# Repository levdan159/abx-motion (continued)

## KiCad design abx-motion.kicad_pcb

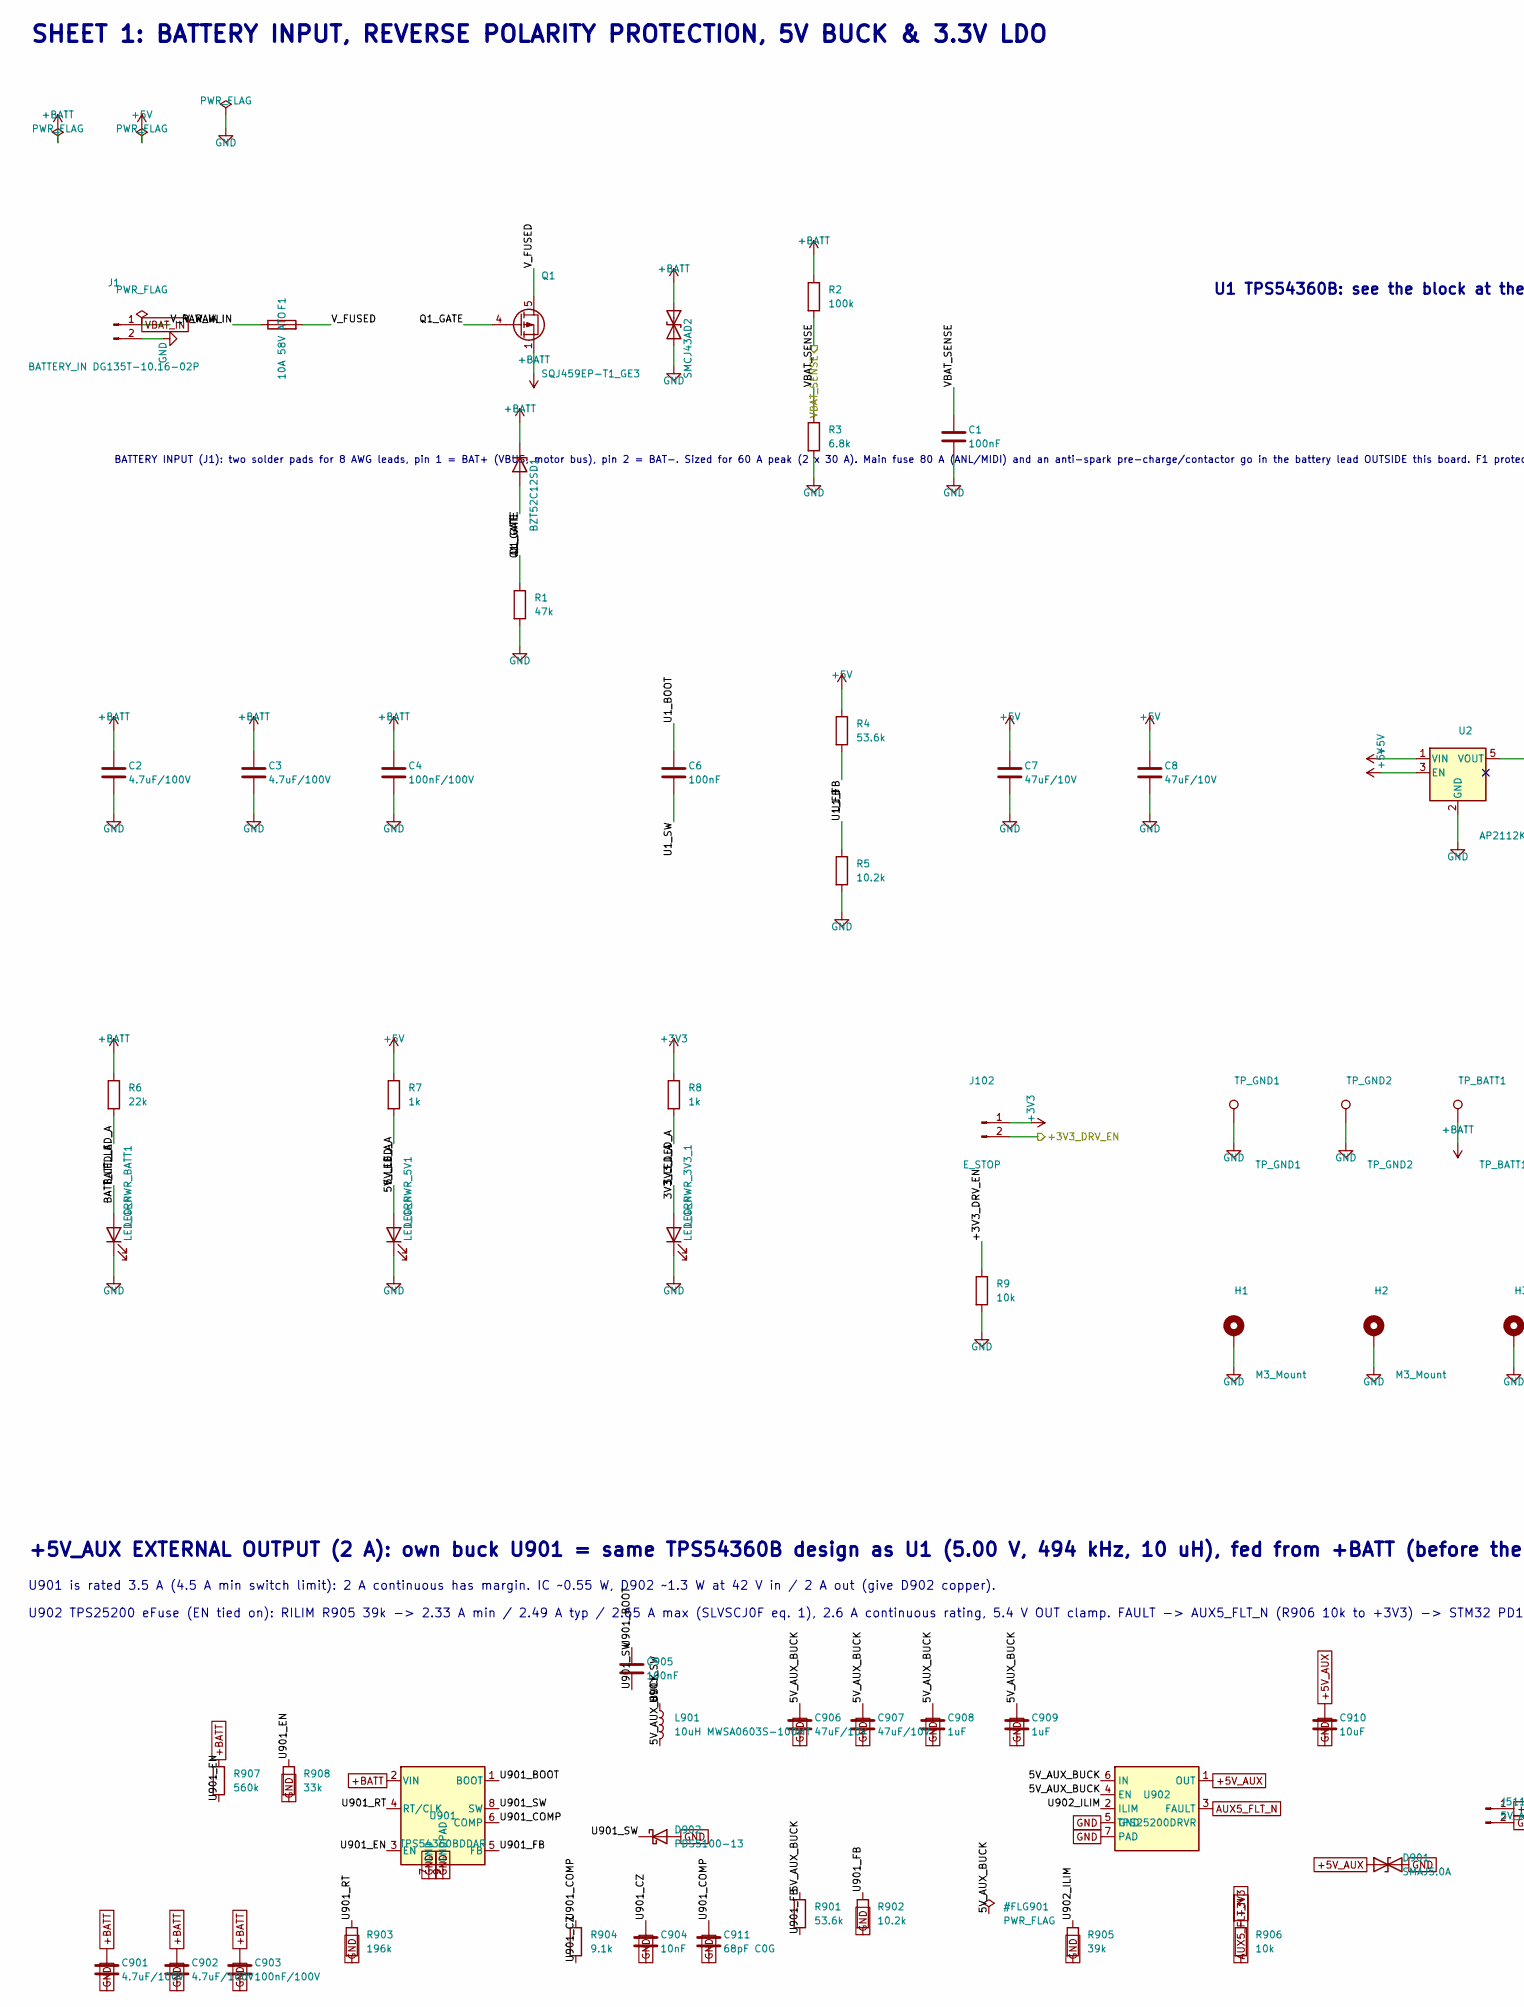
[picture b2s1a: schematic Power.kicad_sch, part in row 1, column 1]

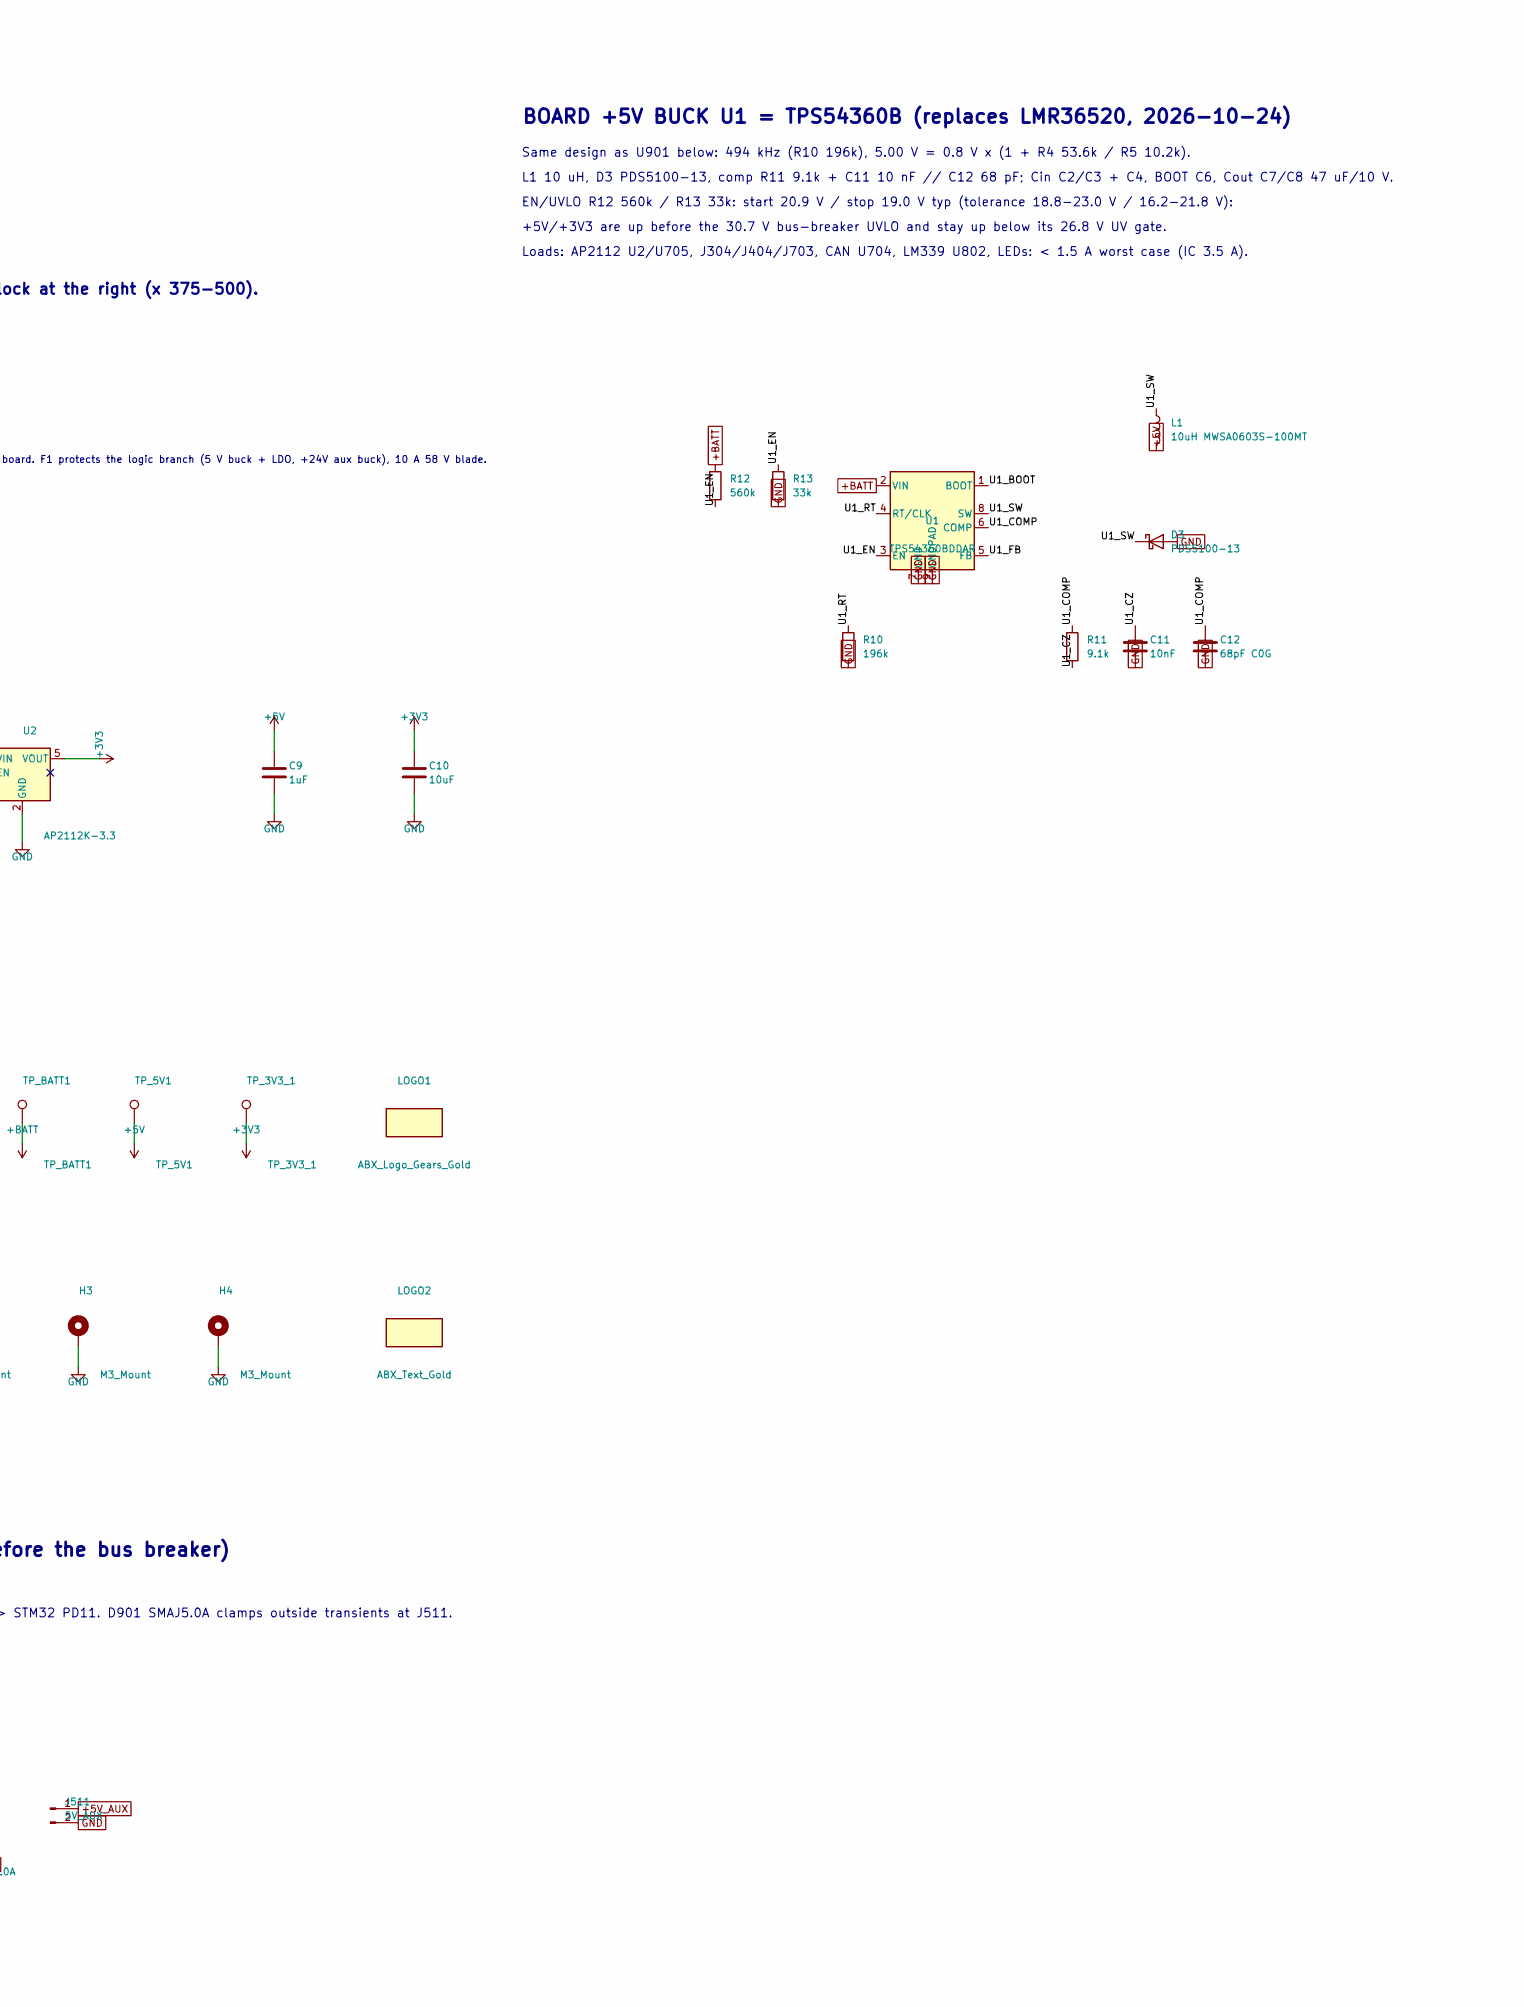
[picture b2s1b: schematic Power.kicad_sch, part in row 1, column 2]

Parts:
C1, C6, C905: 100nF; C_0603_1608Metric
C2, C3, C901, C902: 4.7uF/100V; C_1206_3216Metric
C4, C903: 100nF/100V; C_0603_1608Metric
C7, C8, C906, C907: 47uF/10V; C_1206_3216Metric
C9, C908, C909: 1uF; C_0603_1608Metric
C10, C910: 10uF; C_0805_2012Metric
C11, C904: 10nF; C_0603_1608Metric
C12, C911: 68pF C0G; C_0603_1608Metric
D1: BZT52C12S; D_SOD-323
D2: SMCJ43A; D_SMC
D3, D902: PDS5100-13; D_PowerDI-5
D901: SMAJ5.0A; D_SMA
F1: 10A 58V ATO; Fuseholder_Keystone_3557-2
H1, H2, H3, H4: M3_Mount; MountingHole_3.2mm_M3_Pad_Via
J1: BATTERY_IN DG135T-10.16-02P; ABX_Degson_DG135T-10.16-02P
J102: E_STOP; TerminalBlock_Phoenix_MKDS-1,5-2-5.08_1x02_P5.08mm_Horizont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
J511: 5V_AUX; TerminalBlock_Phoenix_MKDS-1,5-2-5.08_1x02_P5.08mm_Horizont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
L1, L901: 10uH MWSA0603S-100MT; L_Sunlord_MWSA0603S
LED_PWR_3V3_1, LED_PWR_5V1: LED_GRN; LED_0603_1608Metric
LED_PWR_BATT1: LED_GRN; LED_0603_1608Metric
LOGO1: ABX_Logo_Gears_Gold
LOGO2: ABX_Text_Gold
Q1: SQJ459EP-T1_GE3; TDSON-8-1
R1: 47k; R_0603_1608Metric
R2: 100k; R_0603_1608Metric
R3: 6.8k; R_0603_1608Metric
R4, R901: 53.6k; R_0603_1608Metric
R5, R902: 10.2k; R_0603_1608Metric
R6: 22k; R_0603_1608Metric
R7, R8: 1k; R_0603_1608Metric
R9, R906: 10k; R_0603_1608Metric
R10, R903: 196k; R_0603_1608Metric
R11, R904: 9.1k; R_0603_1608Metric
R12, R907: 560k; R_0805_2012Metric
R13, R908: 33k; R_0603_1608Metric
R905: 39k; R_0603_1608Metric
TP_3V3_1: TP_3V3_1; TestPoint_Pad_D1.5mm
TP_5V1: TP_5V1; TestPoint_Pad_D1.5mm
TP_BATT1: TP_BATT1; TestPoint_Pad_D1.5mm
TP_GND1: TP_GND1; TestPoint_Pad_D1.5mm
TP_GND2: TP_GND2; TestPoint_Pad_D1.5mm
U1, U901: TPS54360BDDAR; TI_SO-PowerPAD-8_ThermalVias
U2: AP2112K-3.3; SOT-23-5
U902: TPS25200DRVR; WSON-6-1EP_2x2mm_P0.65mm_EP1x1.6mm_ThermalVias

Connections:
+3V3: C10.1, J102.1, R8.1, TP_3V3_1.1 (1_1), U2.5 (VOUT); also elsewhere on the board
+3V3_DRV_EN: J102.2, R9.1; also elsewhere on the board
+5V: C7.1, C8.1, C9.1, L1.2, R4.1, R7.1, TP_5V1.1 (1_1), U2.1 (VIN), U2.3 (EN); also elsewhere on the board
/Power_Supply/3V3_LED_A: LED_PWR_3V3_1.2 (A), R8.2
/Power_Supply/5V_LED_A: LED_PWR_5V1.2 (A), R7.2
/Power_Supply/BATT_LED_A: LED_PWR_BATT1.2 (A), R6.2
/Power_Supply/Q1_GATE: D1.2 (A), Q1.4 (G), R1.1
/Power_Supply/U1_FB: R4.2, R5.1, U1.5 (FB)
/Power_Supply/U1_SW: C6.2, D3.1 (K), L1.1, U1.8 (SW)
/Power_Supply/U1_VCC: C12.1, R11.1, U1.6 (VCC); also elsewhere on the board
/Power_Supply/V_FUSED: F1.2, Q1.5 (D)
/Power_Supply/V_RAW_IN: F1.1, J1.1
/VBAT_SENSE: C1.1, R2.2, R3.1; also elsewhere on the board
unnamed: C11.1, R11.2
unnamed: C904.1, R904.2
unnamed: C905.1, U901.1 (BOOT)
unnamed: C905.2, D902.1 (K), L901.1, U901.8 (SW)
unnamed: C906.1, C907.1, C908.1, C909.1, L901.2, R901.1, U902.4 (EN), U902.6 (IN)
unnamed: C910.1, D901.1 (A1), J511.1, U902.1 (OUT)
unnamed: C911.1, R904.1, U901.6 (COMP)
unnamed: R10.1, U1.4 (RT/CLK)
unnamed: R901.2, R902.1, U901.5 (FB)
unnamed: R903.1, U901.4 (RT/CLK)
unnamed: R905.1, U902.2 (ILIM)
unnamed: R906.2, U902.3 (FAULT)
unnamed: R907.2, R908.1, U901.3 (EN)

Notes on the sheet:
SHEET 1: BATTERY INPUT, REVERSE POLARITY PROTECTION, 5V BUCK & 3.3V LDO
BATTERY INPUT (J1): two solder pads for 8 AWG leads, pin 1 = BAT+ (VBUS, motor bus), pin 2 = BAT-. Sized for 60 A peak (2 x 30 A). Main fuse 80 A (ANL/MIDI) and an anti-spark pre-charge/contactor go in the battery lead OUTSIDE this board. F1 protects the logic branch (5 V buck + LDO, +24V aux buck)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
BOARD +5V BUCK U1 = TPS54360B (replaces LMR36520, 2026-10-24)
Same design as U901 below: 494 kHz (R10 196k), 5.00 V = 0.8 V x (1 + R4 53.6k / R5 10.2k).
L1 10 uH, D3 PDS5100-13, comp R11 9.1k + C11 10 nF // C12 68 pF; Cin C2/C3 + C4, BOOT C6, Cout C7/C8 47 uF/10 V.
EN/UVLO R12 560k / R13 33k: start 20.9 V / stop 19.0 V typ (tolerance 18.8-23.0 V / 16.2-21.8 V):
+5V/+3V3 are up before the 30.7 V bus-breaker UVLO and stay up below its 26.8 V UV gate.
Loads: AP2112 U2/U705, J304/J404/J703, CAN U704, LM339 U802, LEDs: < 1.5 A worst case (IC 3.5 A).
U1 TPS54360B: see the block at the right (x 375-500).
+5V_AUX EXTERNAL OUTPUT (2 A): own buck U901 = same TPS54360B design as U1 (5.00 V, 494 kHz, 10 uH), fed from +BATT (before the bus breaker)
U901 is rated 3.5 A (4.5 A min switch limit): 2 A continuous has margin. IC ~0.55 W, D902 ~1.3 W at 42 V in / 2 A out (give D902 copper).
U902 TPS25200 eFuse (EN tied on): RILIM R905 39k -> 2.33 A min / 2.49 A typ / 2.65 A max (SLVSCJ0F eq. 1), 2.6 A continuous rating, 5.4 V OUT clamp. FAULT -> AUX5_FLT_N (R906 10k to +3V3) -> STM32 PD11. D901 SMAJ5.0A clamps outside transients at J511.

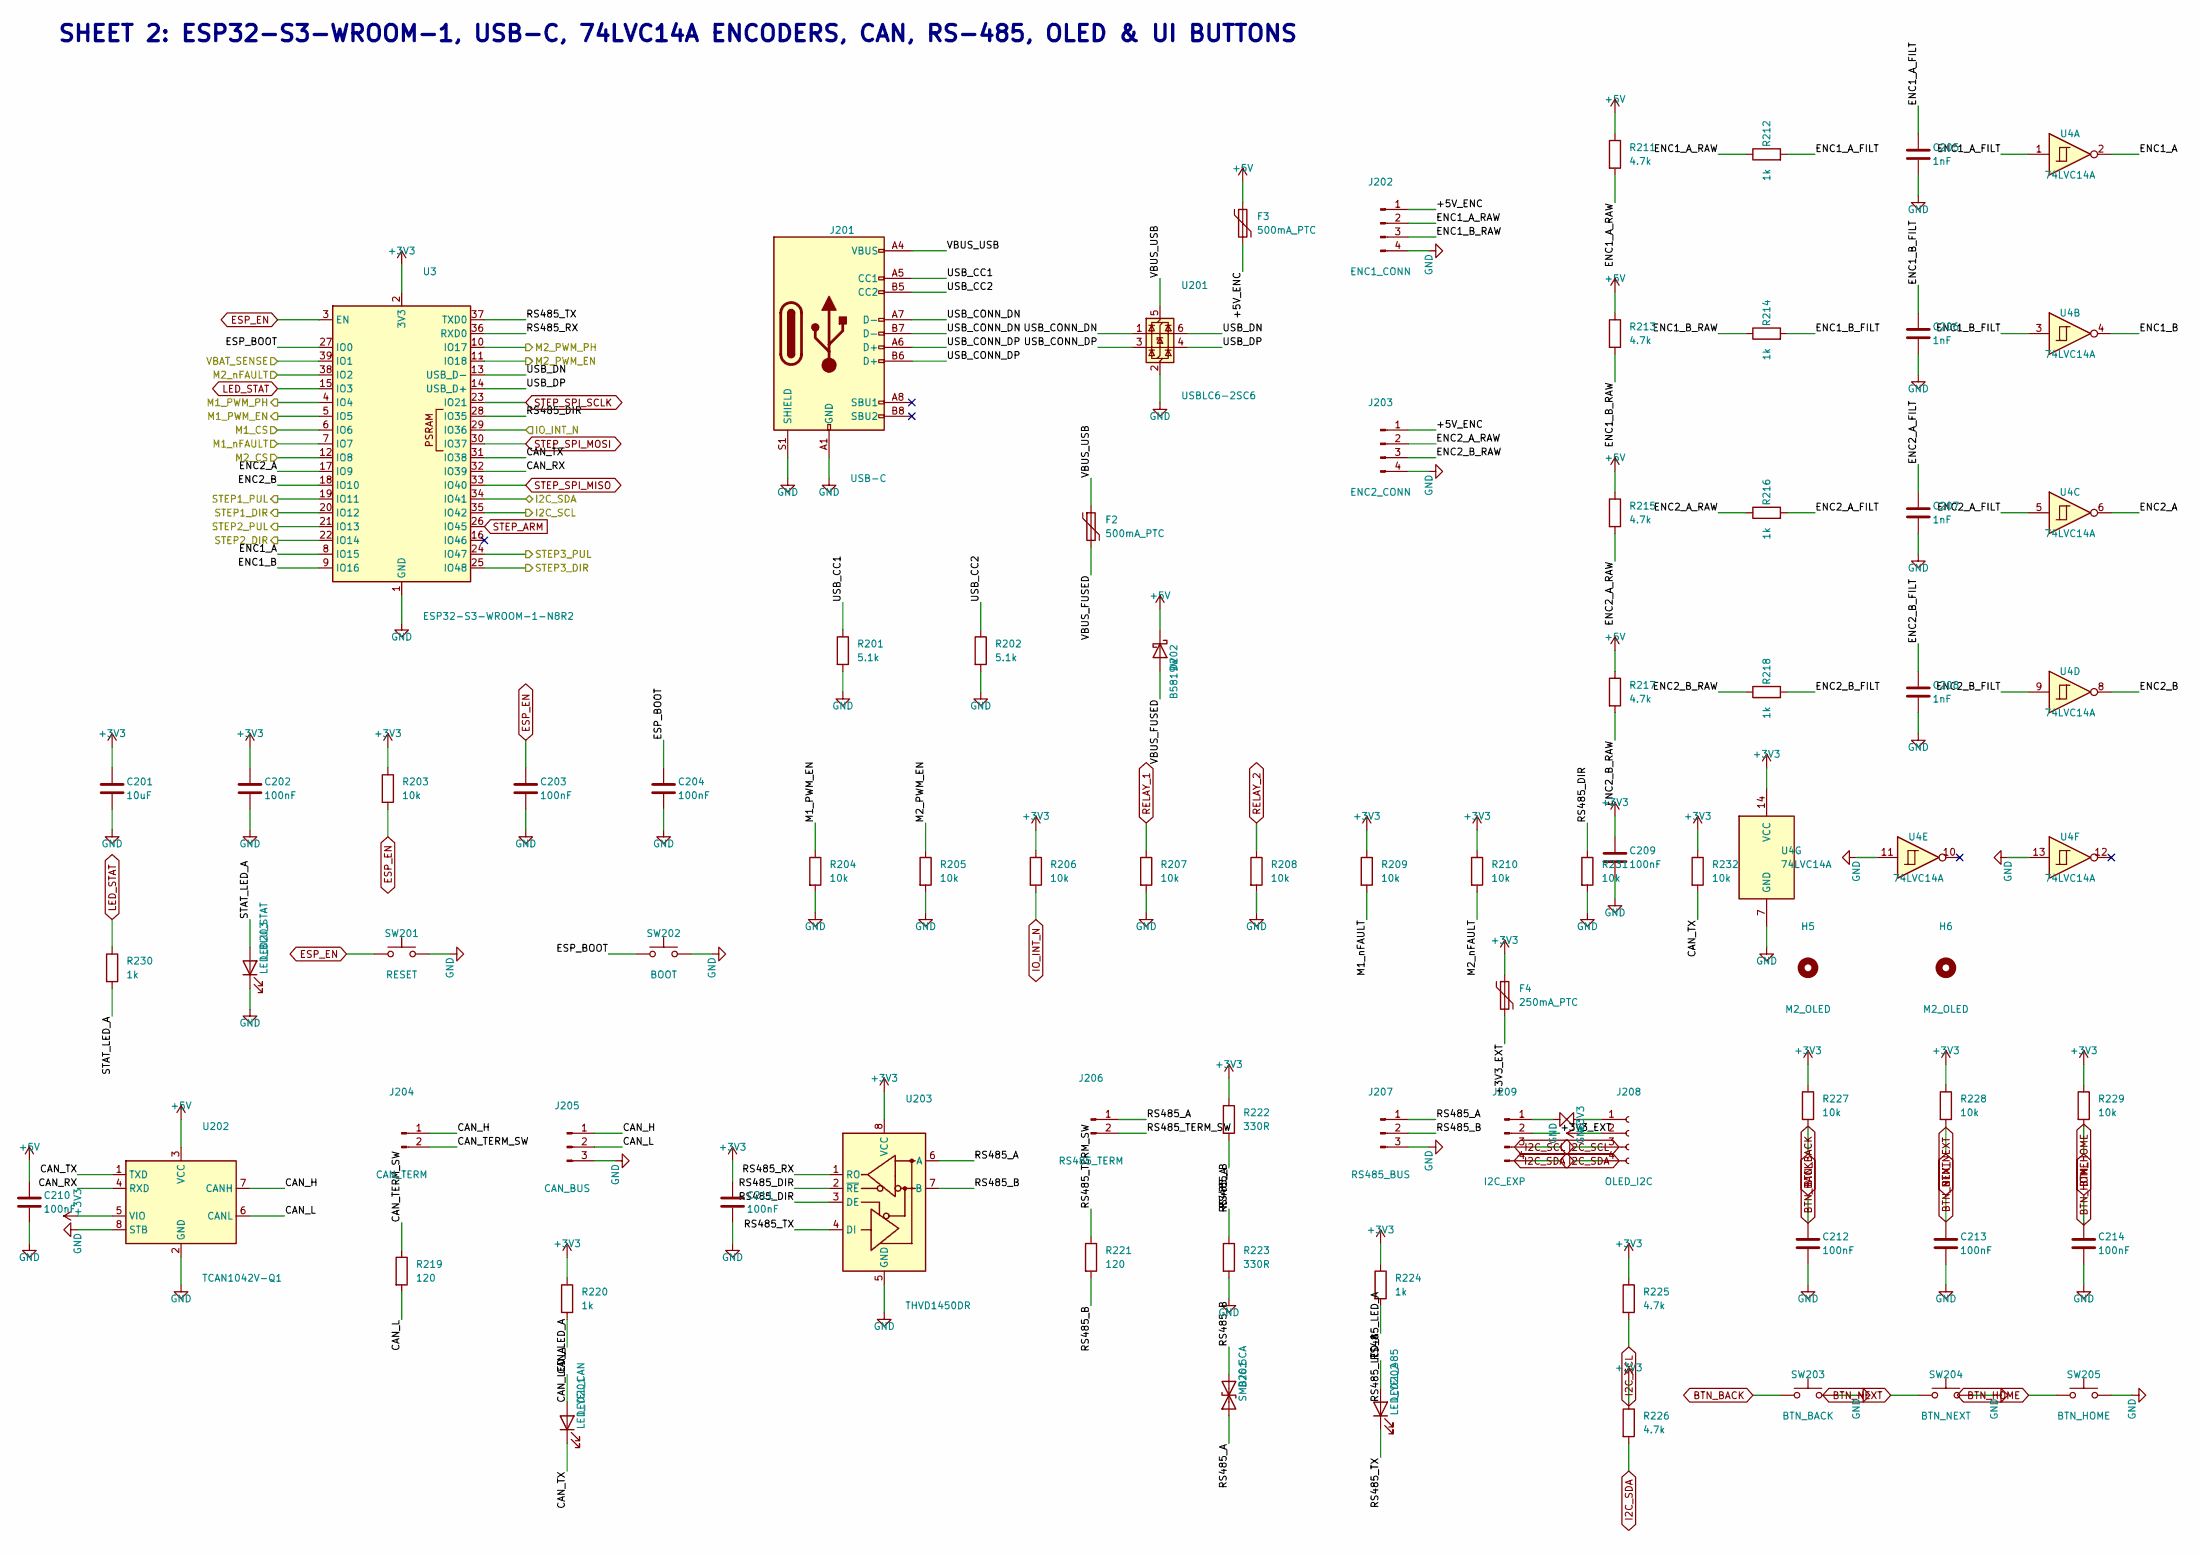
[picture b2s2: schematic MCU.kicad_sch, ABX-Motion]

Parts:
C201: 10uF; C_0805_2012Metric; LCSC C15850
C202, C203, C204, C209, C210, C211, C212, C213, C214: 100nF; C_0603_1608Metric; LCSC C14663
C205, C206, C207, C208: 1nF; C_0603_1608Metric; LCSC C1588
D201: SMBJ6.5CA; D_SMB; LCSC C78428
D202: B5819W; D_SOD-123; LCSC C8598
F2, F3: 500mA_PTC; Fuse_1206_3216Metric; LCSC C2984676
F4: 250mA_PTC; Fuse_1206_3216Metric; LCSC C20798
H5: M2_OLED; ABX_H5_MountingHole_2.2mm_M2
H6: M2_OLED; ABX_H6_MountingHole_2.2mm_M2
J201: USB-C; USB_C_Receptacle_HRO_TYPE-C-31-M-12; LCSC C165948
J202: ENC1_CONN; JST_XH_B4B-XH-A_1x04_P2.50mm_Vertical; LCSC C566014
J203: ENC2_CONN; JST_XH_B4B-XH-A_1x04_P2.50mm_Vertical; LCSC C566014
J204: CAN_TERM; PinHeader_1x02_P2.54mm_Vertical; LCSC C492401
J205: CAN_BUS; ABX_J205_TerminalBlock_Phoenix_MKDS-1_5-3-5.08_1x03_P5.08mm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; LCSC C72334
J206: RS485_TERM; PinHeader_1x02_P2.54mm_Vertical; LCSC C492401
J207: RS485_BUS; ABX_J207_TerminalBlock_Phoenix_MKDS-1_5-3-5.08_1x03_P5.08mm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; LCSC C72334
J208: OLED_I2C; OLED_Socket_SLW_1x04_P2.54mm_LowProfile
J209: I2C_EXP; JST_XH_B4B-XH-A_1x04_P2.50mm_Vertical; LCSC C566014
LED201: LED_YEL_CAN; LED_0603_1608Metric; LCSC C2287
LED202: LED_YEL_485; LED_0603_1608Metric; LCSC C2287
LED203: LED_BLU_STAT; LED_0603_1608Metric; LCSC C2288
R201, R202: 5.1k; R_0603_1608Metric; LCSC C23186
R203, R204, R205, R206, R207, R208, R209, R210, R227, R228, R229, R231, R232: 10k; R_0603_1608Metric; LCSC C25804
R211, R213, R215, R217, R225, R226: 4.7k; R_0603_1608Metric; LCSC C23162
R212, R214, R216, R218, R220, R224, R230: 1k; R_0603_1608Metric; LCSC C21190
R219, R221: 120; R_0603_1608Metric; LCSC C22787
R222, R223: 330R; R_0603_1608Metric; LCSC C23138
SW201: RESET; SW_SPST_B3U-1000P; LCSC C231329
SW202: BOOT; SW_SPST_B3U-1000P; LCSC C231329
SW203: BTN_BACK; SW_SPST_B3U-1000P; LCSC C231329
SW204: BTN_NEXT; SW_SPST_B3U-1000P; LCSC C231329
SW205: BTN_HOME; SW_SPST_B3U-1000P; LCSC C231329
U3: ESP32-S3-WROOM-1-N8R2; ABX_U3_ESP32-S3-WROOM-1; LCSC C2913204
U4: 74LVC14A; SOIC-14_3.9x8.7mm_P1.27mm; LCSC C133541
U201: USBLC6-2SC6; SOT-23-6; LCSC C7519
U202: TCAN1042V-Q1; SOIC-8_3.9x4.9mm_P1.27mm; LCSC C132550
U203: THVD1450DR; SOIC-8_3.9x4.9mm_P1.27mm; LCSC C2671361

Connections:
+3V3: C201.1, C202.1, C209.1, C211.1, F4.1, J208.2, R203.1, R206.1, R209.1, R210.1, R220.1, R222.1, R224.1, R225.1, R226.1, R227.1, R228.1, R229.1, R232.1, U3.2 (3V3), U4.14 (VCC), U202.5 (VIO), U203.8 (VCC); also elsewhere on the board
+5V: C210.1, D202.1 (K), F3.1, R211.1, R213.1, R215.1, R217.1, U202.3 (VCC); also elsewhere on the board
/M1_CS: U3.6 (IO6); also elsewhere on the board
/M1_PWM_EN: R204.1, U3.5 (IO5); also elsewhere on the board
/M1_PWM_PH: U3.4 (IO4); also elsewhere on the board
/M1_nFAULT: R209.2, U3.7 (IO7); also elsewhere on the board
/M2_CS: U3.12 (IO8); also elsewhere on the board
/M2_PWM_EN: R205.1, U3.11 (IO18); also elsewhere on the board
/M2_PWM_PH: U3.10 (IO17); also elsewhere on the board
/M2_nFAULT: R210.2, U3.38 (IO2); also elsewhere on the board
/MCU_and_Encoders/+3V3_EXT: F4.2, J209.2
/MCU_and_Encoders/+5V_ENC: F3.2, J202.1, J203.1
/MCU_and_Encoders/CAN_H: J204.1, J205.1, U202.7 (CANH)
/MCU_and_Encoders/CAN_L: J205.2, R219.2, U202.6 (CANL)
/MCU_and_Encoders/CAN_LED_A: LED201.2 (A), R220.2
/MCU_and_Encoders/CAN_RX: U3.32 (IO39), U202.4 (RXD)
/MCU_and_Encoders/CAN_TERM_SW: J204.2, R219.1
/MCU_and_Encoders/CAN_TX: LED201.1 (K), R232.2, U3.31 (IO38), U202.1 (TXD)
/MCU_and_Encoders/ENC1_A: U3.8 (IO15), U4.2
/MCU_and_Encoders/ENC1_A_FILT: C205.1, R212.2, U4.1
/MCU_and_Encoders/ENC1_A_RAW: J202.2, R211.2, R212.1
/MCU_and_Encoders/ENC1_B: U3.9 (IO16), U4.4
/MCU_and_Encoders/ENC1_B_FILT: C206.1, R214.2, U4.3
/MCU_and_Encoders/ENC1_B_RAW: J202.3, R213.2, R214.1
/MCU_and_Encoders/ENC2_A: U3.17 (IO9), U4.6
/MCU_and_Encoders/ENC2_A_FILT: C207.1, R216.2, U4.5
/MCU_and_Encoders/ENC2_A_RAW: J203.2, R215.2, R216.1
/MCU_and_Encoders/ENC2_B: U3.18 (IO10), U4.8
/MCU_and_Encoders/ENC2_B_FILT: C208.1, R218.2, U4.9
/MCU_and_Encoders/ENC2_B_RAW: J203.3, R217.2, R218.1
/MCU_and_Encoders/ESP_BOOT: C204.1, SW202.1, U3.27 (IO0)
/MCU_and_Encoders/RS485_A: D201.1 (A1), J206.1, J207.1, R222.2, U203.6 (A)
/MCU_and_Encoders/RS485_B: D201.2 (A2), J207.2, R221.2, R223.1, U203.7 (B)
/MCU_and_Encoders/RS485_DIR: R231.1, U3.28 (IO35), U203.2 (~RE), U203.3 (DE)
/MCU_and_Encoders/RS485_LED_A: LED202.2 (A), R224.2
/MCU_and_Encoders/RS485_RX: U3.36 (RXD0), U203.1 (RO)
/MCU_and_Encoders/RS485_TERM_SW: J206.2, R221.1
/MCU_and_Encoders/RS485_TX: LED202.1 (K), U3.37 (TXD0), U203.4 (DI)
/MCU_and_Encoders/STAT_LED_A: LED203.2 (A), R230.2
/MCU_and_Encoders/USB_CC1: J201.A5 (CC1), R201.1
/MCU_and_Encoders/USB_CC2: J201.B5 (CC2), R202.1
/MCU_and_Encoders/USB_CONN_DN: J201.A7 (D-), J201.B7 (D-), U201.1 (I/O1)
/MCU_and_Encoders/USB_CONN_DP: J201.A6 (D+), J201.B6 (D+), U201.3 (I/O2)
/MCU_and_Encoders/USB_DN: U3.13 (USB_D-), U201.6 (I/O1)
/MCU_and_Encoders/USB_DP: U3.14 (USB_D+), U201.4 (I/O2)
/MCU_and_Encoders/VBUS_FUSED: D202.2 (A), F2.2
/MCU_and_Encoders/VBUS_USB: F2.1, J201.A4 (VBUS), J201.A9 (VBUS), J201.B4 (VBUS), J201.B9 (VBUS), U201.5 (VBUS)
/VBAT_SENSE: U3.39 (IO1); also elsewhere on the board
BTN_BACK: C212.1, R227.2, SW203.1; also elsewhere on the board
BTN_HOME: C214.1, R229.2, SW205.1; also elsewhere on the board
BTN_NEXT: C213.1, R228.2, SW204.1; also elsewhere on the board
ESP_EN: C203.1, R203.2, SW201.1, U3.3 (EN); also elsewhere on the board
I2C_SCL: J208.3, J209.3, R225.2, U3.35 (IO42); also elsewhere on the board
I2C_SDA: J208.4, J209.4, R226.2, U3.34 (IO41); also elsewhere on the board
IO_INT_N: R206.2, U3.29 (IO36); also elsewhere on the board
LED_STAT: R230.1, U3.15 (IO3); also elsewhere on the board
RELAY_1: R207.1; also elsewhere on the board
RELAY_2: R208.1; also elsewhere on the board
STEP1_DIR: U3.20 (IO12); also elsewhere on the board
STEP1_PUL: U3.19 (IO11); also elsewhere on the board
STEP2_DIR: U3.22 (IO14); also elsewhere on the board
STEP2_PUL: U3.21 (IO13); also elsewhere on the board
STEP3_DIR: U3.25 (IO48); also elsewhere on the board
STEP3_PUL: U3.24 (IO47); also elsewhere on the board
STEP_ARM: U3.26 (IO45); also elsewhere on the board
STEP_SPI_MISO: U3.33 (IO40); also elsewhere on the board
STEP_SPI_MOSI: U3.30 (IO37); also elsewhere on the board
STEP_SPI_SCLK: U3.23 (IO21); also elsewhere on the board

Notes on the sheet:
SHEET 2: ESP32-S3-WROOM-1, USB-C, 74LVC14A ENCODERS, CAN, RS-485, OLED & UI BUTTONS

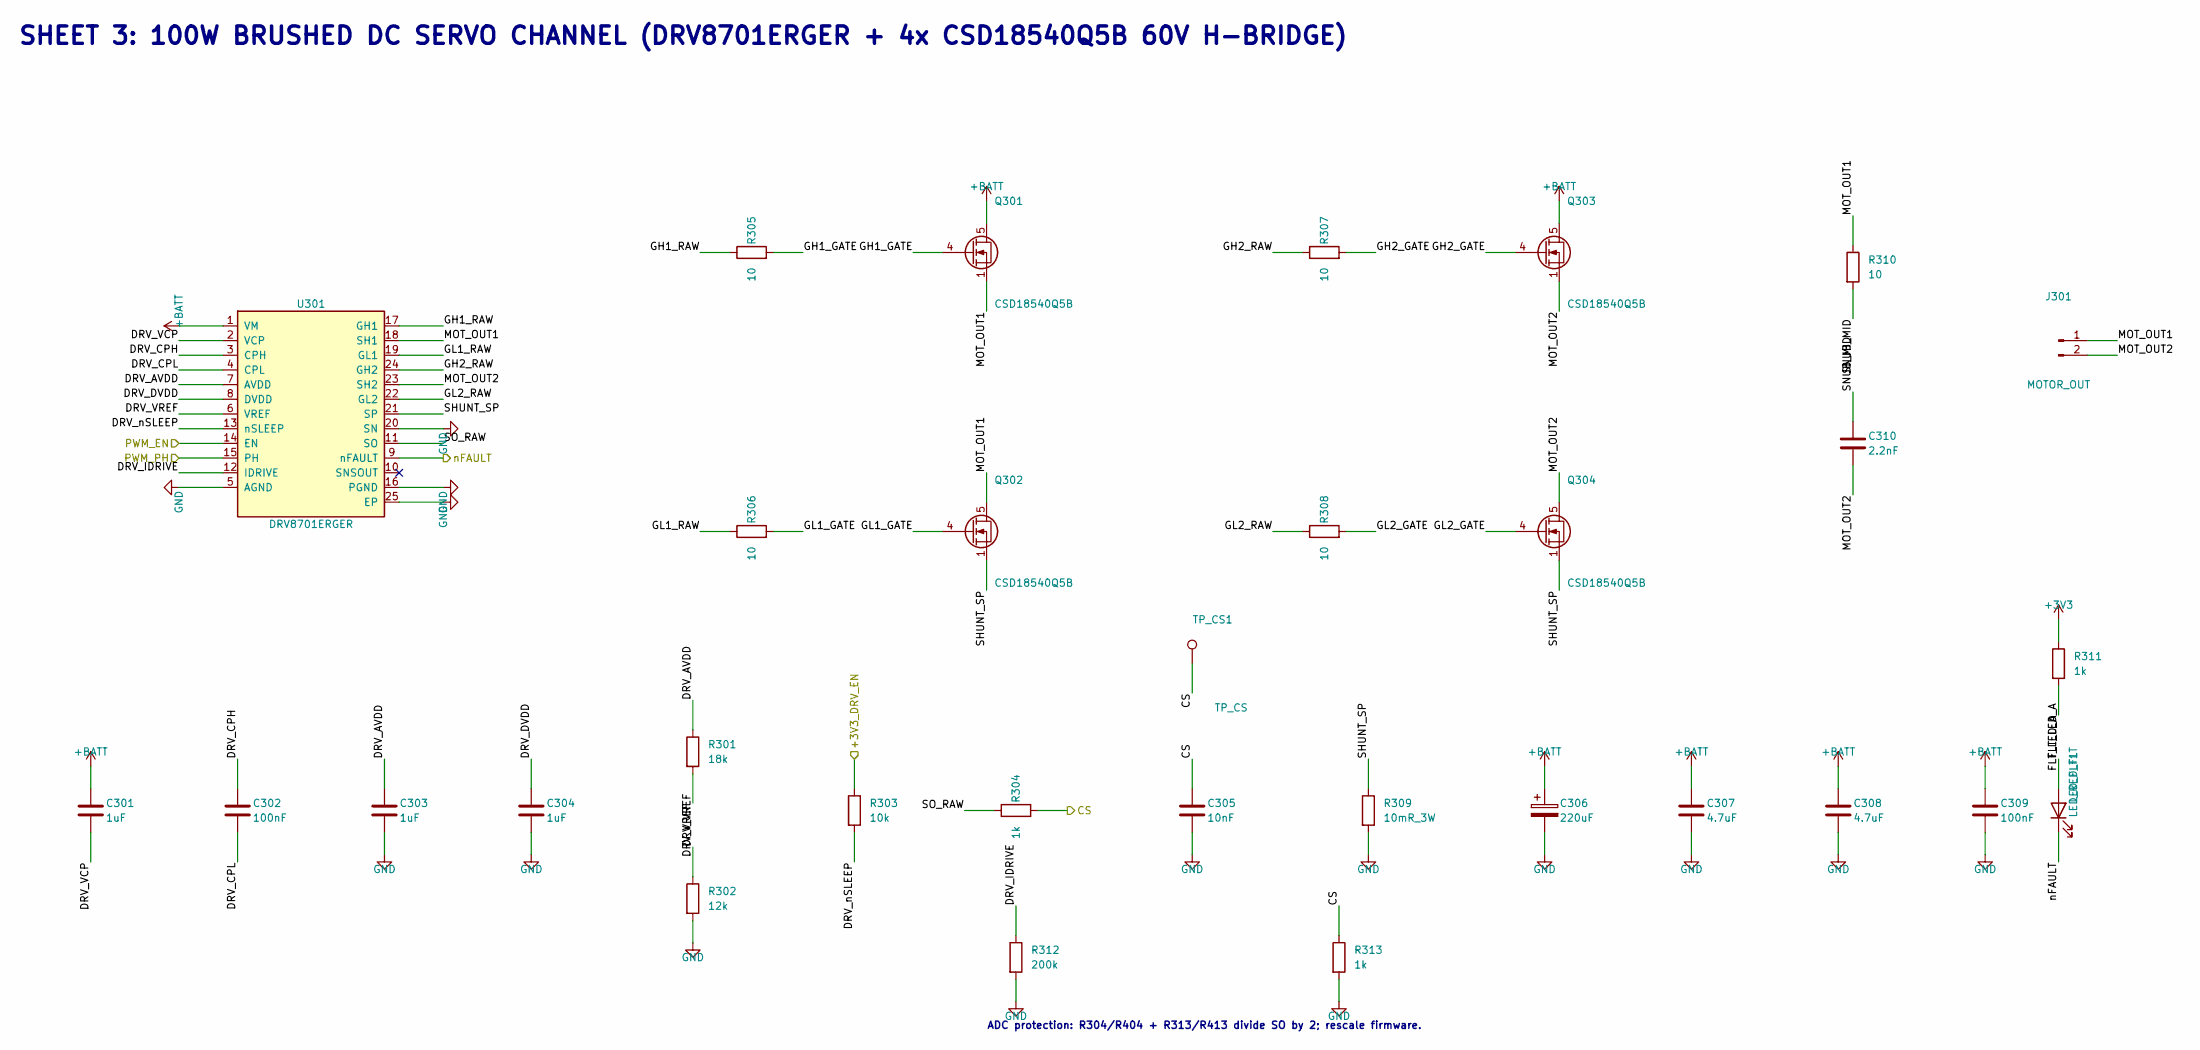
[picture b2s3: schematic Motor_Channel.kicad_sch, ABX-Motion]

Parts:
C301, C303, C304: 1uF; C_0603_1608Metric; LCSC C15849
C302, C309: 100nF; C_0603_1608Metric; LCSC C14663
C305: 10nF; C_0603_1608Metric; LCSC C57112
C306: 220uF; CP_Elec_10x10.5; LCSC C72499
C307, C308: 4.7uF; C_1206_3216Metric; LCSC C29823
C310: 2.2nF; C_0805_2012Metric; LCSC C107136
J301: MOTOR_OUT; MKDS_2Pin_Motor_ABX; LCSC C8465
LED_FLT1: LED_RED_FLT; LED_0603_1608Metric; LCSC C2286
Q301, Q302, Q303, Q304: CSD18540Q5B; TDSON-8-1; LCSC C86513
R301: 18k; R_0603_1608Metric; LCSC C25810
R302: 12k; R_0603_1608Metric; LCSC C22790
R303: 10k; R_0603_1608Metric; LCSC C25804
R304, R311, R313: 1k; R_0603_1608Metric; LCSC C21190
R305, R306, R307, R308: 10; R_0603_1608Metric; LCSC C22859
R309: 10mR_3W; R_2512_6332Metric; LCSC C840621
R310: 10; R_0805_2012Metric; LCSC C844598
R312: 200k; R_0603_1608Metric; LCSC C25811
TP_CS1: TP_CS; TestPoint_PTH_2.5x3.6_D1.0_CS_ABX
U301: DRV8701ERGER; DRV8701_RGE_Thermal_ABX; LCSC C90964

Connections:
+3V3: R311.1; also elsewhere on the board
+3V3_DRV_EN: R303.1; also elsewhere on the board
/DC_Motor_1/DRV_AVDD: C303.1, R301.1, U301.7 (AVDD)
/DC_Motor_1/DRV_CPH: C302.1, U301.3 (CPH)
/DC_Motor_1/DRV_CPL: C302.2, U301.4 (CPL)
/DC_Motor_1/DRV_DVDD: C304.1, U301.8 (DVDD)
/DC_Motor_1/DRV_IDRIVE: R312.1, U301.12 (IDRIVE)
/DC_Motor_1/DRV_VCP: C301.2, U301.2 (VCP)
/DC_Motor_1/DRV_VREF: R301.2, R302.1, U301.6 (VREF)
/DC_Motor_1/DRV_nSLEEP: R303.2, U301.13 (nSLEEP)
/DC_Motor_1/FLT_LED_A: LED_FLT1.2 (A), R311.2
/DC_Motor_1/GH1_GATE: Q301.4 (G), R305.2
/DC_Motor_1/GH1_RAW: R305.1, U301.17 (GH1)
/DC_Motor_1/GH2_GATE: Q303.4 (G), R307.2
/DC_Motor_1/GH2_RAW: R307.1, U301.24 (GH2)
/DC_Motor_1/GL1_GATE: Q302.4 (G), R306.2
/DC_Motor_1/GL1_RAW: R306.1, U301.19 (GL1)
/DC_Motor_1/GL2_GATE: Q304.4 (G), R308.2
/DC_Motor_1/GL2_RAW: R308.1, U301.22 (GL2)
/DC_Motor_1/MOT_OUT1: J301.1, Q301.1 (S), Q301.2 (S), Q301.3 (S), Q302.5 (D), R310.1, U301.18 (SH1)
/DC_Motor_1/MOT_OUT2: C310.2, J301.2, Q303.1 (S), Q303.2 (S), Q303.3 (S), Q304.5 (D), U301.23 (SH2)
/DC_Motor_1/SHUNT_SP: Q302.1 (S), Q302.2 (S), Q302.3 (S), Q304.1 (S), Q304.2 (S), Q304.3 (S), R309.1, U301.21 (SP)
/DC_Motor_1/SNUB_MID: C310.1, R310.2
/DC_Motor_1/SO_RAW: R304.1, U301.11 (SO)
/M1_CS: C305.1, R304.2, R313.1, TP_CS1.1 (1_1); also elsewhere on the board
/M1_PWM_EN: U301.14 (PH); also elsewhere on the board
/M1_PWM_PH: U301.15 (EN); also elsewhere on the board
/M1_nFAULT: LED_FLT1.1 (K), U301.9 (nFAULT); also elsewhere on the board

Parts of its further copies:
C401, C403, C404: 1uF; C_0603_1608Metric; LCSC C15849
C402, C409: 100nF; C_0603_1608Metric; LCSC C14663
C405: 10nF; C_0603_1608Metric; LCSC C57112
C406: 220uF; CP_Elec_10x10.5; LCSC C72499
C407, C408: 4.7uF; C_1206_3216Metric; LCSC C29823
C410: 2.2nF; C_0805_2012Metric; LCSC C107136
J401: MOTOR_OUT; MKDS_2Pin_Motor_ABX; LCSC C8465
LED_FLT2: LED_RED_FLT; LED_0603_1608Metric; LCSC C2286
Q401, Q402, Q403, Q404: CSD18540Q5B; TDSON-8-1; LCSC C86513
R401: 18k; R_0603_1608Metric; LCSC C25810
R402: 12k; R_0603_1608Metric; LCSC C22790
R403: 10k; R_0603_1608Metric; LCSC C25804
R404, R411, R413: 1k; R_0603_1608Metric; LCSC C21190
R405, R406, R407, R408: 10; R_0603_1608Metric; LCSC C22859
R409: 10mR_3W; R_2512_6332Metric; LCSC C840621
R410: 10; R_0805_2012Metric; LCSC C844598
R412: 200k; R_0603_1608Metric; LCSC C25811
TP_CS2: TP_CS; TestPoint_PTH_2.5x3.6_D1.0_CS_ABX
U401: DRV8701ERGER; DRV8701_RGE_Thermal_ABX; LCSC C90964

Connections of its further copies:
+3V3: R411.1; also elsewhere on the board
+3V3_DRV_EN: R403.1; also elsewhere on the board
/DC_Motor_2/DRV_AVDD: C403.1, R401.1, U401.7 (AVDD)
/DC_Motor_2/DRV_CPH: C402.1, U401.3 (CPH)
/DC_Motor_2/DRV_CPL: C402.2, U401.4 (CPL)
/DC_Motor_2/DRV_DVDD: C404.1, U401.8 (DVDD)
/DC_Motor_2/DRV_IDRIVE: R412.1, U401.12 (IDRIVE)
/DC_Motor_2/DRV_VCP: C401.2, U401.2 (VCP)
/DC_Motor_2/DRV_VREF: R401.2, R402.1, U401.6 (VREF)
/DC_Motor_2/DRV_nSLEEP: R403.2, U401.13 (nSLEEP)
/DC_Motor_2/FLT_LED_A: LED_FLT2.2 (A), R411.2
/DC_Motor_2/GH1_GATE: Q401.4 (G), R405.2
/DC_Motor_2/GH1_RAW: R405.1, U401.17 (GH1)
/DC_Motor_2/GH2_GATE: Q403.4 (G), R407.2
/DC_Motor_2/GH2_RAW: R407.1, U401.24 (GH2)
/DC_Motor_2/GL1_GATE: Q402.4 (G), R406.2
/DC_Motor_2/GL1_RAW: R406.1, U401.19 (GL1)
/DC_Motor_2/GL2_GATE: Q404.4 (G), R408.2
/DC_Motor_2/GL2_RAW: R408.1, U401.22 (GL2)
/DC_Motor_2/MOT_OUT1: J401.1, Q401.1 (S), Q401.2 (S), Q401.3 (S), Q402.5 (D), R410.1, U401.18 (SH1)
/DC_Motor_2/MOT_OUT2: C410.2, J401.2, Q403.1 (S), Q403.2 (S), Q403.3 (S), Q404.5 (D), U401.23 (SH2)
/DC_Motor_2/SHUNT_SP: Q402.1 (S), Q402.2 (S), Q402.3 (S), Q404.1 (S), Q404.2 (S), Q404.3 (S), R409.1, U401.21 (SP)
/DC_Motor_2/SNUB_MID: C410.1, R410.2
/DC_Motor_2/SO_RAW: R404.1, U401.11 (SO)
/M2_CS: C405.1, R404.2, R413.1, TP_CS2.1 (1_1); also elsewhere on the board
/M2_PWM_EN: U401.14 (PH); also elsewhere on the board
/M2_PWM_PH: U401.15 (EN); also elsewhere on the board
/M2_nFAULT: LED_FLT2.1 (K), U401.9 (nFAULT); also elsewhere on the board

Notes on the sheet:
SHEET 3: 100W BRUSHED DC SERVO CHANNEL (DRV8701ERGER + 4x CSD18540Q5B 60V H-BRIDGE)
ADC protection: R304/R404 + R313/R413 divide SO by 2; rescale firmware.
